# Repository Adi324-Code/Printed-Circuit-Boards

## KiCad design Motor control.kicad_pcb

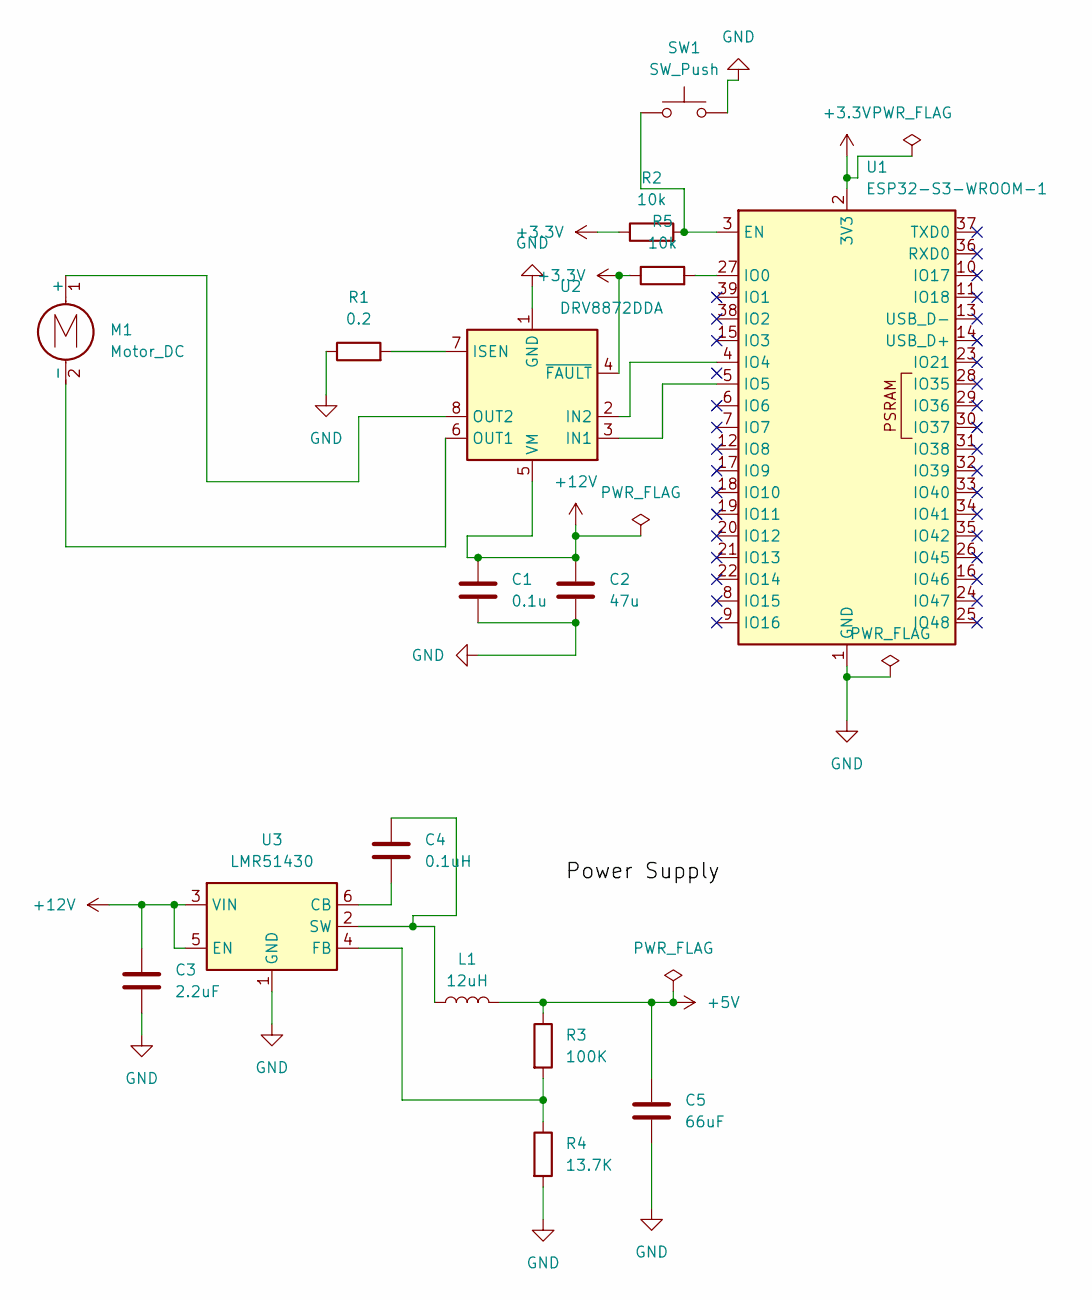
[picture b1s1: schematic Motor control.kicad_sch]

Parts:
C1: 0.1u; C_0603_1608Metric
C2: 47u; C_1210_3225Metric
C3: 2.2uF; C_0603_1608Metric
C4: 0.1uH; C_0603_1608Metric
C5: 66uF; C_1210_3225Metric
L1: 12uH; L_1812_4532Metric
M1: Motor_DC; Vybronics_VZ30C1T8219732L
R1: 0.2; R_0603_1608Metric
R2, R5: 10k; R_1218_3246Metric
R3: 100K; R_1218_3246Metric
R4: 13.7K; R_1218_3246Metric
SW1: SW_Push; SW_PUSH_6mm_H5mm
U1: ESP32-S3-WROOM-1
U2: DRV8872DDA; HTSOP-8-1EP_3.9x4.9mm_P1.27mm_EP2.4x3.2mm_ThermalVias
U3: LMR51430; SOT-23-6

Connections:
+3.3V: R2.1, R5.1, U1.2 (3V3), U2.4 (~FAULT)
+5V: C5.1, L1.2, R3.1
+12V: C1.1, C2.1, C3.1, U2.5 (VM), U3.3 (VIN), U3.5 (EN)
GND: C1.2, C2.2, C3.2, C5.2, R1.1, R4.2, SW1.2, U1.1 (GND), U1.40 (GND), U1.41 (GND), U2.1 (GND), U2.9 (GND), U3.1 (GND)
unnamed: M1.1 (+), U2.8 (OUT2)
unnamed: M1.2 (-), U2.6 (OUT1)
unnamed: R2.2, SW1.1, U1.3 (EN)
unnamed: R5.2, U1.27 (IO0)
unnamed: U1.4 (IO4), U2.2 (IN2)
unnamed: U1.5 (IO5), U2.3 (IN1)
unnamed: R1.2, U2.7 (ISEN)
unnamed: C4.2, U3.6 (CB)
unnamed: R3.2, R4.1, U3.4 (FB)
unnamed: C4.1, L1.1, U3.2 (SW)

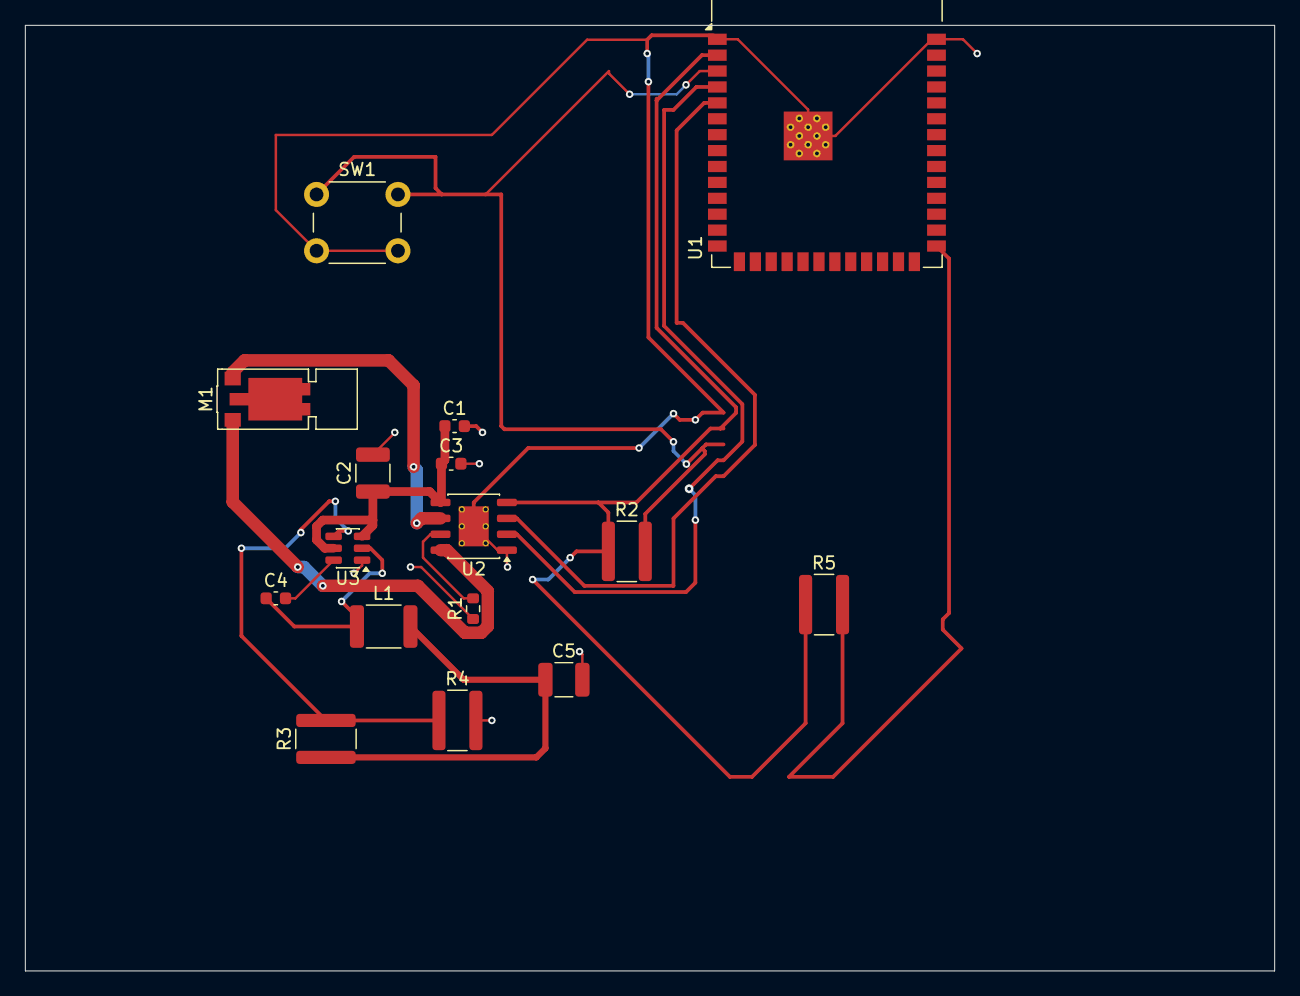
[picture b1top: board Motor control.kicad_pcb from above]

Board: 2 copper layers, 99.8 x 75.5 mm, 16 parts (0 on the bottom side), 14 nets.
